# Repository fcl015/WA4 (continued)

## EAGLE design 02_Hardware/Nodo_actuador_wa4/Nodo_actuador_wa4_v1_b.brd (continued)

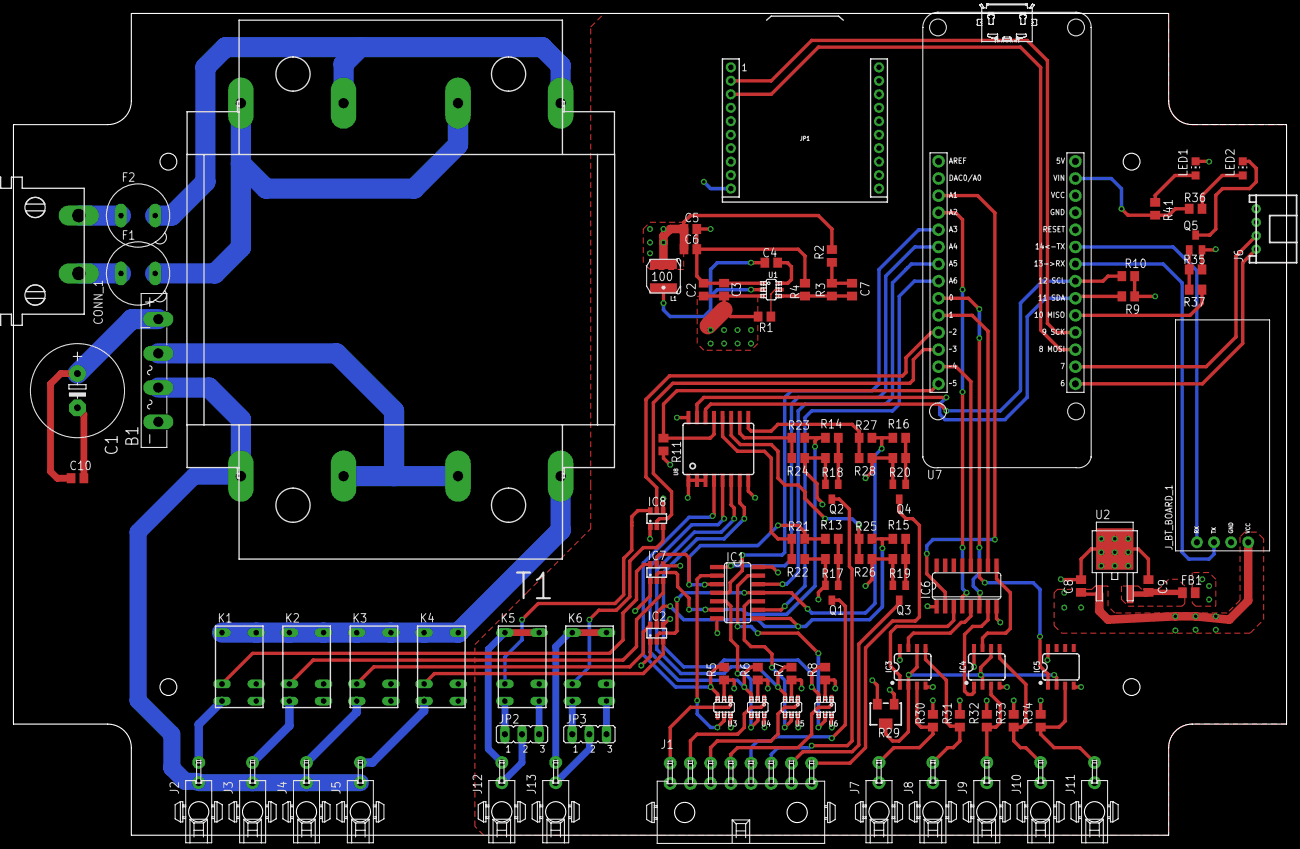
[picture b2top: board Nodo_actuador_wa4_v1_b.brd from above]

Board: 4 copper layers, 189.0 x 122.0 mm, 100 parts (0 on the bottom side), 99 nets.

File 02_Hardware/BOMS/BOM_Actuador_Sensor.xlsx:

BOM: NODO ACTUADOR WA4 V1
Cantidad | Componente | Descripcion | Valor | No. Parte | Fabricante | Link | Costo unitario | Costo total | Aplicación | Notas
1 | CONN_1 | Conector AC C-8 | - | 2570-2210 | Schurter | Mouser | 0.88400000000000001 | 0.88400000000000001 | Conector de alimentacion principal
1 | T1 | Transformador | 24 V 48VA | FP24-2000 | Triad Magnetics | Mouser | 22.97 | 22.97 | Fuente de alimentacion principal
1 | B1 | Puente rectificador | 4A | GBU4J | ON Semiconductor | Mouser | 1.52 | 1.52 | Fuente de alimentacion principal
1 | U1 | Regulador Buck | 500 KHz | TPS54202HDDCR | Texas Instruments | Mouser | 2.1800000000000002 | 2.1800000000000002 | Fuente de 5V
1 | C1 | Capacitor electrolitico | 1000 uF 25V | ECA-1EHG102 | Panasonic | Mouser | 0.96199999999999997 | 0.96199999999999997
2 | C2,C10 | Capacitor ceramico | 10 uF 16V | GRM21BC81C106KA73L | Murata | Mouser | 0.66300000000000003 | 1.3260000000000001
3 | C3,C4,C9 | Capacitor ceramico | 0.1 uF | 08053C104KAT2A | AVX | Mouser | 0.23400000000000001 | 0.70200000000000007
1 | R1 | Resistencia | 510 kΩ | RR1220P-514-D | Susumu | Mouser | 0.13 | 0.13
1 | R2 | Resistencia | 51 Ω | RR1220Q-510-D | Susumu | Mouser | 0.13 | 0.13
1 | R3 | Resistencia | 100 kΩ | RR1220P-104-D | Susumu | Mouser | 0.13 | 0.13
1 | R4 | Resistencia | 13.3 kΩ | RR1220P-1332-D-M | Susumu | Mouser | 0.14299999999999999 | 0.14299999999999999
2 | C5,C6 | Capacitor ceramico | 22 uF 6.3V | GRM219R60J226MEA0D | Murata | Mouser | 0.46800000000000003 | 0.93600000000000005
1 | C7 | Capacitor ceramico | 75 pF | 08051A750JAT2A | AVX | Mouser | 0.377 | 0.377
1 | L1 | Inductor | 15 uH | VLS5045EX-150M-CA | TDK | Mouser | 0.754 | 0.754
1 | C8 | Capacitor ceramico | 0.33 uF | 885012207048 | Wurth Electronics | Mouser | 0.14299999999999999 | 0.14299999999999999
1 | U2 | Regulador lineal | 3.3V | UA78M33IKVURG3 | Texas Instruments | Mouser | 1.01 | 1.01 | Fuente de 3.3V
40 | - | Contacto para cable | - | 1-794606-2 | Te Connectivity | Mouser | 0.10100000000000001 | 4.04 | Contactos para cables de botones, LEDs, sensores de flujo y valvulas
1 |  | Conector hembra 16 pin | 16 pin 2 rows | 4-794619-6 | Te Connectivity | Mouser | 3.17 | 3.17 | Conector para botones y LEDs
1 | - | Conector macho 16 pin | 16 pin 2 rows | 1-794617-6 | Te Connectivity | Mouser | 1.1399999999999999 | 1.1399999999999999 | Conector para botones y LEDs
11 |  | Conector hembra 2 pin | 2 pin 2 rows | 3-794618-2 | Te Connectivity | Mouser | 1 | 11 | Conectores para valvulas y sensores
11 | - | Conector macho 2 pin | 2 pin 2 rows | 794617-2 | Te Connectivity | Mouser | 0.66300000000000003 | 7.2930000000000001 | Conectores para valvulas y sensores
1 | IC1 | Puertas lógicas 2-6V Quad OR | - | MC74HC32ADR2G | ON Semiconductor | Mouser | 0.55900000000000005 | 0.55900000000000005 | Para control de valvulas por boton o por software
4 | U3-U6 | Controlador push button | - | MAX16054AZT+T | Maxim Integrated | Mouser | 3.37 | 13.48 | Eliminación de rebote y proteccion ESD
17 | R5-R11,R17-R20,R22,R24,R26,R28,R35,R37 | Resistencia | 10 kΩ | RR1220P-103-D | Susumu | Mouser | 0.13 | 2.21
6 | K1-K6 | Relevador | 5 VDC | G5V-1-2 DC5 | Omron | Mouser | 2.85 | 17.100000000000001 | Relevadores para valvulas y activacion de bomba
3 | IC2,IC7,IC8 | Driver relevador | - | MDC3105DMT1G | ON Semiconductor | Mouser | 0.57199999999999995 | 1.7159999999999997
4 | R13-R16 | Resistencia | 1 kΩ | RR1220P-102-D | Susumu | Mouser | 0.13 | 0.52
5 | Q1-Q5 | Transistor BJT NPN | - | BCX70K | ON Semiconductor | Mouser | 0.377 | 1.885 | Encendido de LEDs de los botones
4 | - | Push button con LED | Azul | 481 | Adafruit | Mouser / Adafruit | 6.44 | 25.76 | Botones para encendido manual de valvulas
2 | JP1 | XBEE Header | 10 pin | 366 | Adafruit | Mouser | 1.24 | 2.48 | Socket Xbee
1 | R29 | Potenciometro | 50 kΩ | PVG5A503C03B00 | Bourns | Mouser | 3.3 | 3.3 | Referencia de voltaje para sensores de flujo
4 | R21,R23,R25,R27 | Resistencia | 5.1 kΩ | RR1220P-512-D | Susumu | Mouser | 0.13 | 0.52
3 | IC3,IC4,IC5 | Amplificador operacional | - | LM358ADR | Texas Instruments | Mouser | 0.46800000000000003 | 1.4040000000000001 | Lectura de sensor de flujo
1 | IC6 | Buffer no inversor | - | CD4050BDR | Texas Instruments | Mouser | 0.54600000000000004 | 0.54600000000000004 | Acondicionamiento de señal de sensor de flujo
5 | R30-R34 | Resistencia | 330 Ω 0.5W 0.5% | SG73G2ATTD3300D | KOA | Mouser | 0.29899999999999999 | 1.4949999999999999
2 | LED1-LED2 | LED | Verde | LTST-C170GKT | Lite On | Mouser | 0.39 | 0.78 | Indicadores
2 | R36,R41 | Resistencia | 330 Ω | RR1220P-331-D | Susumu | Mouser | 0.13 | 0.26
1 | U8 | Expansion IO | - | PCF8574DWR | Texas Instruments | Mouser | 1.95 | 1.95
2 | - | Header Arduino | 14 pin | M20-7821446 | Harwin | Mouser | 1.87 | 3.74
1 | FB1 | Ferrita | - | MPZ2012S102JTD25 | TDK | Mouser | 0.16900000000000001 | 0.16900000000000001
1 | - | Header | 4 pin | M20-7820446 | Harwin | Mouser | 1.03 | 1.03
1 | - | Antenna con cable | - | ANT-916-PML-UFL | Linx Technologies | Mouser | 12.74 | 12.74
 |  |  |  |  |  |  | Total | 154.584

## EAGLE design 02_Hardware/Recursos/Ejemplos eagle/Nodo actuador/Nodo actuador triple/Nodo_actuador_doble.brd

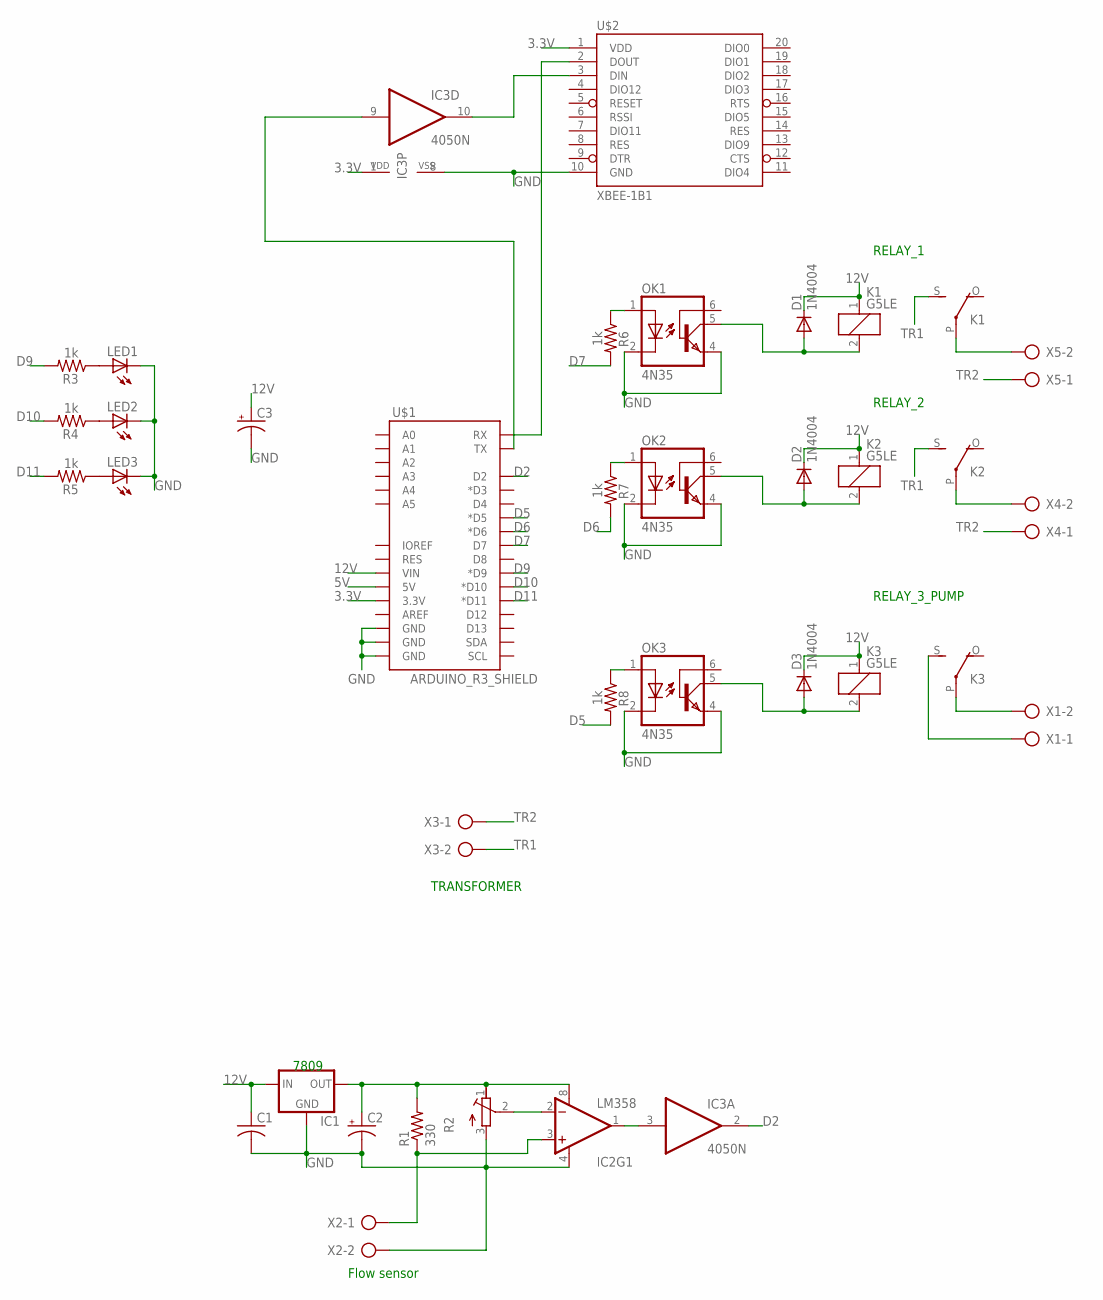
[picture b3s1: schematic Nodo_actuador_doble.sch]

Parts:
C1: C-US050-024X044; C050-024X044
C2, C3: CPOL-USE2.5-6; E2,5-6
D1, D2, D3: 1N4004; DO41-10
IC1: 78XXS
IC2: LM358; DIP08
IC3: 4050N; DIL16
K1, K2, K3: G5LE
LED1, LED2, LED3: LED3MM
OK1, OK2, OK3: 4N35; DIL06
R1: 330; 0204/7
R2: R-TRIMMT93YA; RTRIMT93YA
R3, R4, R5, R6, R7, R8: 1k; 0204/7
U$1: ARDUINO_R3_SHIELD; UNO_R3_SHIELD
U$2: XBEE-1B1; XBEE-1
X1, X2, X3, X4, X5: AK500/2

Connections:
3.3V: IC3.1 (VDD), U$1.3.3V, U$2.1 (VDD)
5V: U$1.5V
12V: C1.1, C3.+, D1.C, D2.C, D3.C, IC1.IN, K1.1, K2.1, K3.1, U$1.VIN
D2: IC3.2 (O), U$1.D2
D5: R8.2, U$1.D5 (*D5)
D6: R7.2, U$1.D6 (*D6)
D7: R6.2, U$1.D7
D9: R3.2, U$1.D9 (*D9)
D10: R4.2, U$1.D10 (*D10)
D11: R5.2, U$1.D11 (*D11)
GND: C1.2, C2.-, C3.-, IC1.GND, IC2.4 (V-), IC3.8 (VSS), LED1.K (C), LED2.K (C), LED3.K (C), OK1.2 (C), OK1.4 (EMI), OK2.2 (C), OK2.4 (EMI), OK3.2 (C), OK3.4 (EMI), R2.3 (E), U$1.GND@0 (GND), U$1.GND@1 (GND), U$1.GND@2 (GND), U$2.10 (GND), X2.2
unnamed: LED1.A, R3.1
unnamed: LED2.A, R4.1
unnamed: LED3.A, R5.1
unnamed: IC2.3 (+IN), R1.1, X2.1
unnamed: C2.+, IC1.OUT, IC2.8 (V+), R1.2, R2.1 (A)
unnamed: IC2.1 (OUT), IC3.3 (I)
unnamed: IC2.2 (-IN), R2.2 (S)
unnamed: K1.P, X5.2
unnamed: D1.A, K1.2, OK1.5 (COL)
unnamed: K2.P, X4.2
unnamed: D2.A, K2.2, OK2.5 (COL)
unnamed: U$1.RX, U$2.2 (DOUT)
unnamed: IC3.9 (I), U$1.TX
unnamed: IC3.10 (O), U$2.3 (DIN)
unnamed: D3.A, K3.2, OK3.5 (COL)
unnamed: K3.P, X1.2
unnamed: K3.S, X1.1
unnamed: OK1.1 (A), R6.1
unnamed: OK2.1 (A), R7.1
unnamed: OK3.1 (A), R8.1
TR1: K1.S, K2.S, X3.2
TR2: X3.1, X4.1, X5.1

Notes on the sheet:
7809
Flow sensor
TRANSFORMER
RELAY_1
RELAY_2
RELAY_3_PUMP

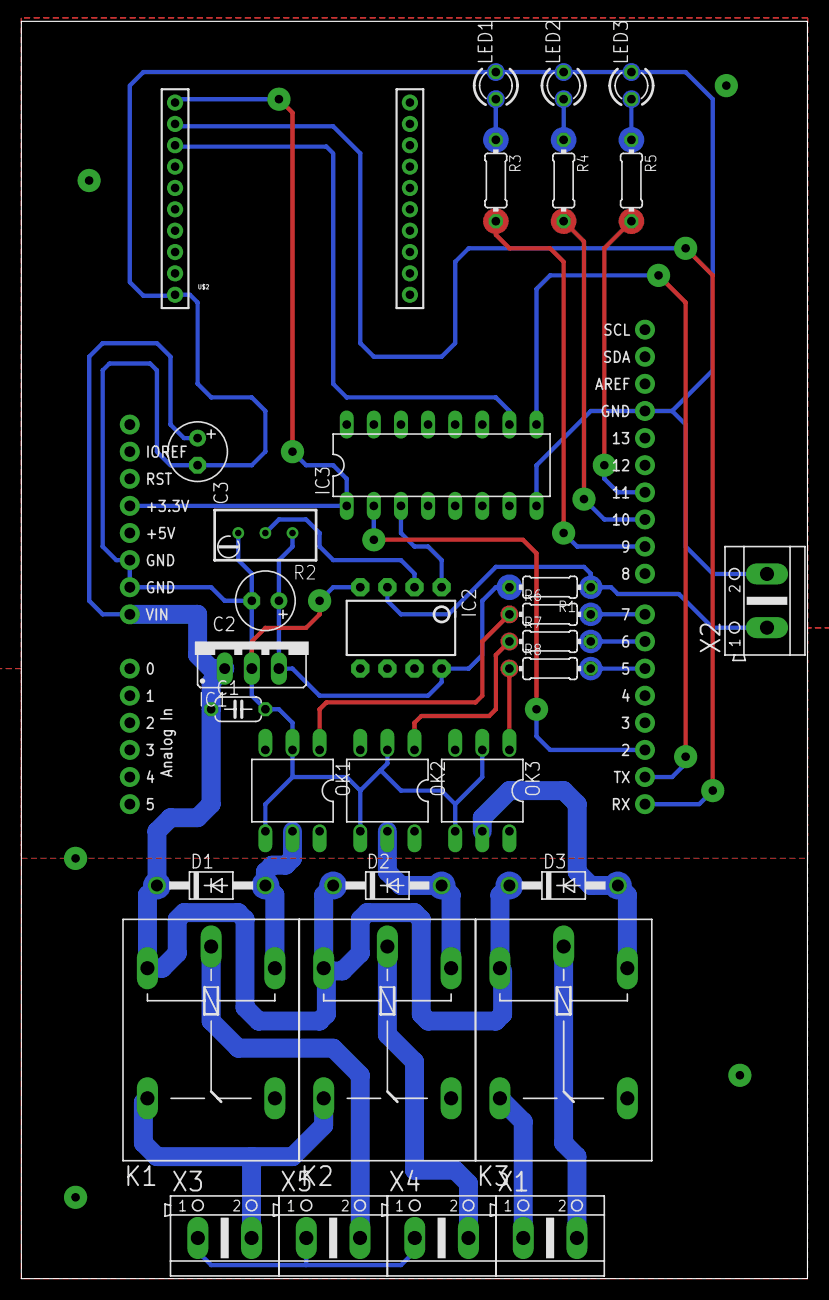
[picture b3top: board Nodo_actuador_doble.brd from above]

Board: 2 copper layers, 73.6 x 117.8 mm, 33 parts (0 on the bottom side), 32 nets.

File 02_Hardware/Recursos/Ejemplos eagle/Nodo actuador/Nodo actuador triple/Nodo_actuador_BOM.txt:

Partlist exported from C:/Users/Carlos/Documents/eagle/Nodo actuador triple/Nodo_actuador_doble.sch at 12/04/2015 02:19:37 p. m.

Part Value             Device            Package       Description                                     MF                      MPN  OC_FARNELL OC_NEWARK PROD_ID 
C1                     C-US050-024X044   C050-024X044  CAPACITOR, American symbol                                                                                
C2                     CPOL-USE2.5-6     E2,5-6        POLARIZED CAPACITOR, American symbol                                                                      
C3                     CPOL-USE2.5-6     E2,5-6        POLARIZED CAPACITOR, American symbol                                                                      
D1   1N4004            1N4004            DO41-10       DIODE                                                                                                     
D2   1N4004            1N4004            DO41-10       DIODE                                                                                                     
D3   1N4004            1N4004            DO41-10       DIODE                                                                                                     
IC1                    78XXS             78XXS         VOLTAGE REGULATOR                                                                                         
IC2  LM358             LM358             DIP08         Jellybean op-amp                                                                                  IC-09172
IC3  4050N             4050N             DIL16         Hex non-inverting BUFFER                                                                                  
K1   G5LE              G5LE              G5LE          RELAY                                                                        unknown    unknown           
K2   G5LE              G5LE              G5LE          RELAY                                                                        unknown    unknown           
K3   G5LE              G5LE              G5LE          RELAY                                                                        unknown    unknown           
LED1                   LED3MM            LED3MM        LED                                                                                                       
LED2                   LED3MM            LED3MM        LED                                                                                                       
LED3                   LED3MM            LED3MM        LED                                                                                                       
OK1  4N35              4N35              DIL06         MOTOROLA OPTO COUPLER                           FAIRCHILD SEMICONDUCTOR 4N35 1328375    72K9946           
OK2  4N35              4N35              DIL06         MOTOROLA OPTO COUPLER                           FAIRCHILD SEMICONDUCTOR 4N35 1328375    72K9946           
OK3  4N35              4N35              DIL06         MOTOROLA OPTO COUPLER                           FAIRCHILD SEMICONDUCTOR 4N35 1328375    72K9946           
R1   330               R-US_0204/7       0204/7        RESISTOR, American symbol                                                                                 
R2                     R-TRIMMT93YA      RTRIMT93YA    Trimm resistor                                                                                            
R3   1k                R-US_0204/7       0204/7        RESISTOR, American symbol                                                                                 
R4   1k                R-US_0204/7       0204/7        RESISTOR, American symbol                                                                                 
R5   1k                R-US_0204/7       0204/7        RESISTOR, American symbol                                                                                 
R6   1k                R-US_0204/7       0204/7        RESISTOR, American symbol                                                                                 
R7   1k                R-US_0204/7       0204/7        RESISTOR, American symbol                                                                                 
R8   1k                R-US_0204/7       0204/7        RESISTOR, American symbol                                                                                 
U$1  ARDUINO_R3_SHIELD ARDUINO_R3_SHIELD UNO_R3_SHIELD Shield form compatible with the Arduino Uno R3.                                                           
U$2  XBEE-1B1          XBEE-1B1          XBEE-1        Xbee module footprints                                                                                    
X1                     AK500/2           AK500/2       CONNECTOR                                                                    unknown    unknown           
X2                     AK500/2           AK500/2       CONNECTOR                                                                    unknown    unknown           
X3                     AK500/2           AK500/2       CONNECTOR                                                                    unknown    unknown           
X4                     AK500/2           AK500/2       CONNECTOR                                                                    unknown    unknown           
X5                     AK500/2           AK500/2       CONNECTOR                                                                    unknown    unknown

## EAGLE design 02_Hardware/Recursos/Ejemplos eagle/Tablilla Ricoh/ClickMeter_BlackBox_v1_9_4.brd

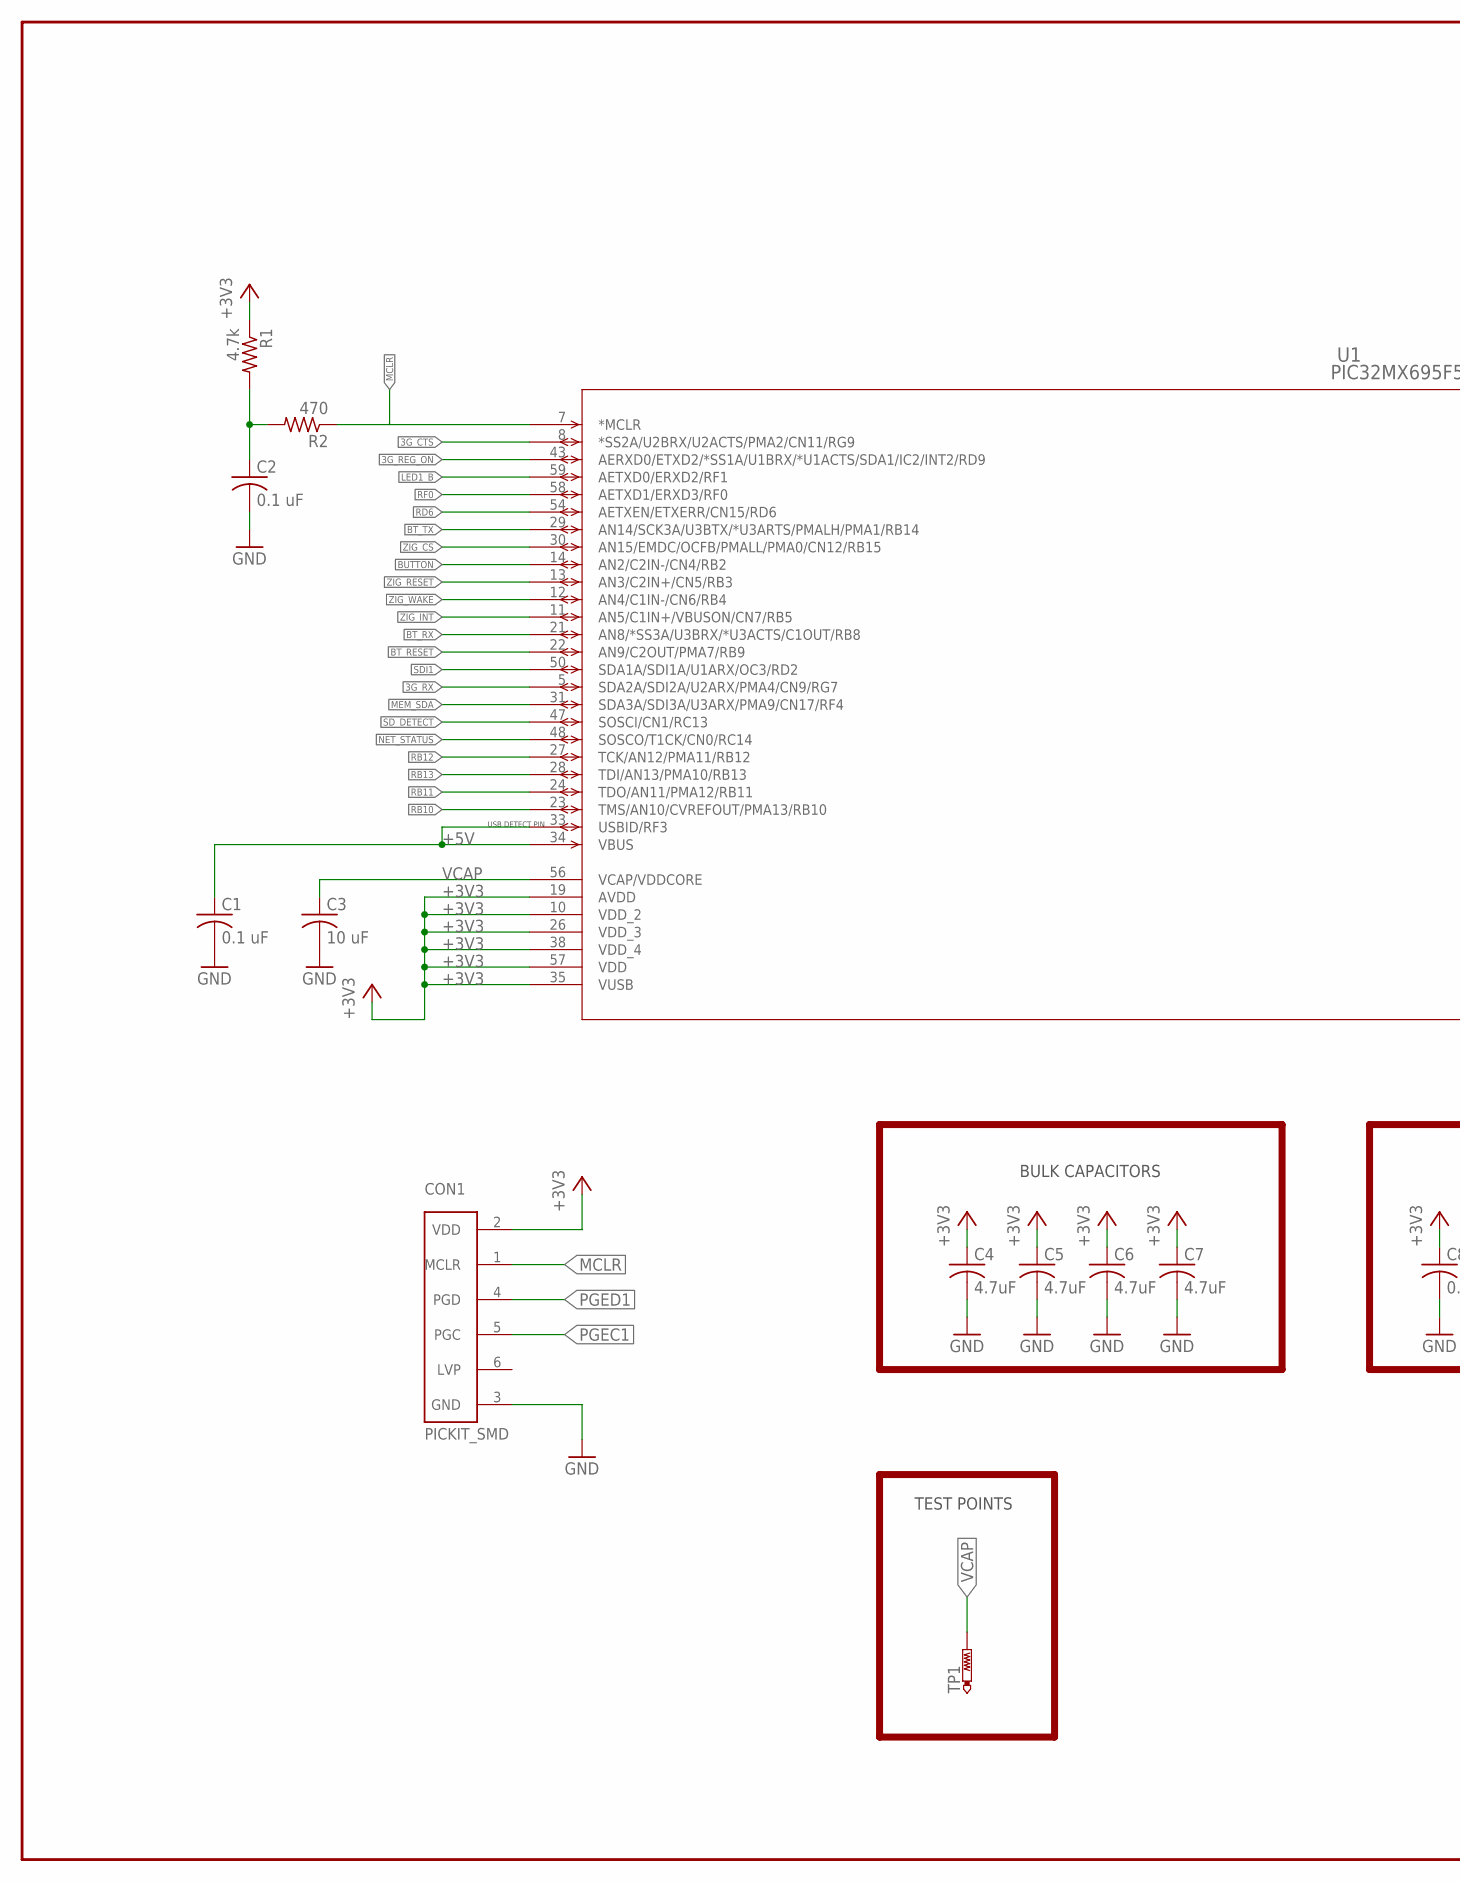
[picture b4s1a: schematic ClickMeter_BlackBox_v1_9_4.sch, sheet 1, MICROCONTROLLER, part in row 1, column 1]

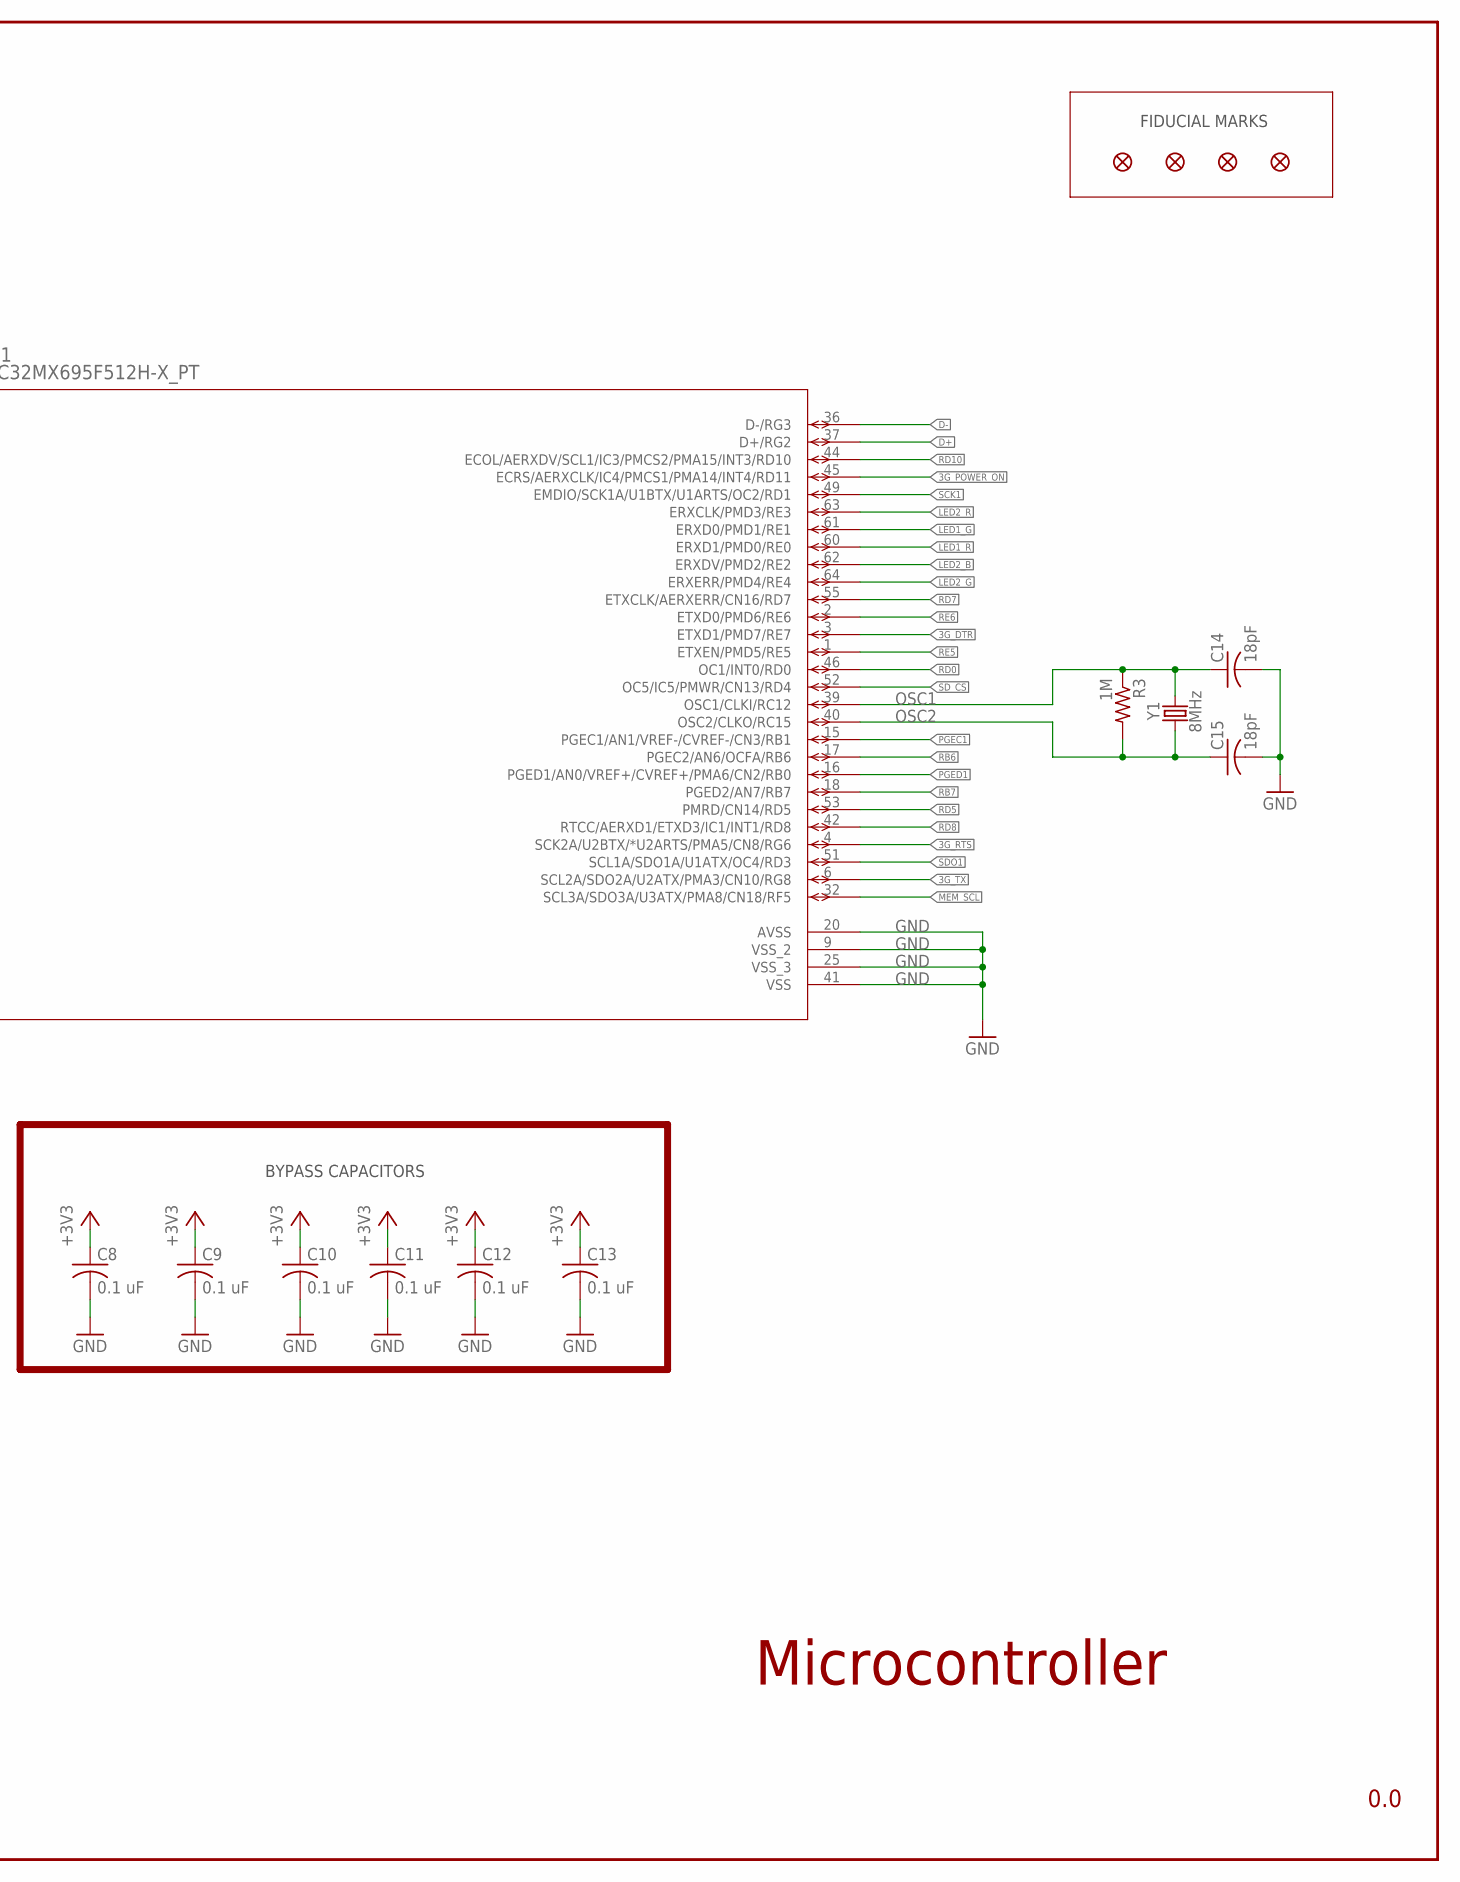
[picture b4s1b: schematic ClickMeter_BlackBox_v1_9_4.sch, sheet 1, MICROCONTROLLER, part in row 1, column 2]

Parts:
C1, C2, C8, C9, C10, C11, C12, C13: 0.1 uF; C0603
C3: 10 uF; C0805
C4, C5, C6, C7: 4.7uF; C0603
C14, C15: 18pF; C0603
CON1: PICKIT_SMD; SMD_PICKIT
F1, F2, F3, F4: FIDUCIAL
R1: 4.7k; R0603
R2: 470; R0603
R3: 1M; R0603
TP1: PTR1B1,27; B1,27
U1: PIC32MX695F512H-X_PT; TQFP64_10X10MC
Y1: 8MHz; CRYSTAL-TXC-7A

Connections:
3G_CTS: U1.8 (*SS2A/U2BRX/U2ACTS/PMA2/CN11/RG9); also elsewhere on the board
3G_DTR: U1.3 (ETXD1/PMD7/RE7); also elsewhere on the board
3G_POWER_ON: U1.45 (ECRS/AERXCLK/IC4/PMCS1/PMA14/INT4/RD11); also elsewhere on the board
3G_REG_ON: U1.43 (AERXD0/ETXD2/*SS1A/U1BRX/*U1ACTS/SDA1/I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)
3G_RTS: U1.4 (SCK2A/U2BTX/*U2ARTS/PMA5/CN8/RG6); also elsewhere on the board
3G_RX: U1.5 (SDA2A/SDI2A/U2ARX/PMA4/CN9/RG7); also elsewhere on the board
3G_TX: U1.6 (SCL2A/SDO2A/U2ATX/PMA3/CN10/RG8); also elsewhere on the board
+3V3: C4.1, C5.1, C6.1, C7.1, C8.1, C9.1, C10.1, C11.1, C12.1, C13.1, CON1.2 (VDD), R1.1, U1.10 (VDD_2), U1.19 (AVDD), U1.26 (VDD_3), U1.35 (VUSB), U1.38 (VDD_4), U1.57 (VDD); also elsewhere on the board
+5V: C1.1, U1.33 (USBID/RF3), U1.34 (VBUS); also elsewhere on the board
BT_RESET: U1.22 (AN9/C2OUT/PMA7/RB9); also elsewhere on the board
BT_RX: U1.21 (AN8/*SS3A/U3BRX/*U3ACTS/C1OUT/RB8); also elsewhere on the board
BT_TX: U1.29 (AN14/SCK3A/U3BTX/*U3ARTS/PMALH/PMA1/RB14); also elsewhere on the board
BUTTON: U1.14 (AN2/C2IN-/CN4/RB2); also elsewhere on the board
D+: U1.37 (D+/RG2); also elsewhere on the board
D-: U1.36 (D-/RG3); also elsewhere on the board
GND: C1.2, C2.2, C3.2, C4.2, C5.2, C6.2, C7.2, C8.2, C9.2, C10.2, C11.2, C12.2, C13.2, C14.2, C15.2, CON1.3 (GND), U1.9 (VSS_2), U1.20 (AVSS), U1.25 (VSS_3), U1.41 (VSS); also elsewhere on the board
LED1_B: U1.59 (AETXD0/ERXD2/RF1); also elsewhere on the board
LED1_G: U1.61 (ERXD0/PMD1/RE1); also elsewhere on the board
LED1_R: U1.60 (ERXD1/PMD0/RE0); also elsewhere on the board
LED2_B: U1.62 (ERXDV/PMD2/RE2); also elsewhere on the board
LED2_G: U1.64 (ERXERR/PMD4/RE4); also elsewhere on the board
LED2_R: U1.63 (ERXCLK/PMD3/RE3); also elsewhere on the board
MCLR: CON1.1 (MCLR), R2.1, U1.7 (*MCLR)
MEM_SCL: U1.32 (SCL3A/SDO3A/U3ATX/PMA8/CN18/RF5); also elsewhere on the board
MEM_SDA: U1.31 (SDA3A/SDI3A/U3ARX/PMA9/CN17/RF4); also elsewhere on the board
unnamed: C2.1, R1.2, R2.2
NET_STATUS: U1.48 (SOSCO/T1CK/CN0/RC14); also elsewhere on the board
OSC1: C14.1, R3.1, U1.39 (OSC1/CLKI/RC12), Y1.P$2 (2)
OSC2: C15.1, R3.2, U1.40 (OSC2/CLKO/RC15), Y1.P$1 (1)
PGEC1: CON1.5 (PGC), U1.15 (PGEC1/AN1/VREF-/CVREF-/CN3/RB1)
PGED1: CON1.4 (PGD), U1.16 (PGED1/AN0/VREF+/CVREF+/PMA6/CN2/RB0)
RB6: U1.17 (PGEC2/AN6/OCFA/RB6)
RB7: U1.18 (PGED2/AN7/RB7)
RB10: U1.23 (TMS/AN10/CVREFOUT/PMA13/RB10)
RB11: U1.24 (TDO/AN11/PMA12/RB11)
RB12: U1.27 (TCK/AN12/PMA11/RB12)
RB13: U1.28 (TDI/AN13/PMA10/RB13)
RD0: U1.46 (OC1/INT0/RD0)
RD5: U1.53 (PMRD/CN14/RD5)
RD6: U1.54 (AETXEN/ETXERR/CN15/RD6)
RD7: U1.55 (ETXCLK/AERXERR/CN16/RD7)
RD8: U1.42 (RTCC/AERXD1/ETXD3/IC1/INT1/RD8)
RD10: U1.44 (ECOL/AERXDV/SCL1/IC3/PMCS2/PMA15/INT3/R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)
RE5: U1.1 (ETXEN/PMD5/RE5)
RE6: U1.2 (ETXD0/PMD6/RE6)
RF0: U1.58 (AETXD1/ERXD3/RF0)
SCK1: U1.49 (EMDIO/SCK1A/U1BTX/U1ARTS/OC2/RD1); also elsewhere on the board
SDI1: U1.50 (SDA1A/SDI1A/U1ARX/OC3/RD2); also elsewhere on the board
SDO1: U1.51 (SCL1A/SDO1A/U1ATX/OC4/RD3); also elsewhere on the board
SD_CS: U1.52 (OC5/IC5/PMWR/CN13/RD4); also elsewhere on the board
SD_DETECT: U1.47 (SOSCI/CN1/RC13); also elsewhere on the board
VCAP: C3.1, TP1.TP, U1.56 (VCAP/VDDCORE)
ZIG_CS: U1.30 (AN15/EMDC/OCFB/PMALL/PMA0/CN12/RB15)
ZIG_INT: U1.11 (AN5/C1IN+/VBUSON/CN7/RB5)
ZIG_RESET: U1.13 (AN3/C2IN+/CN5/RB3)
ZIG_WAKE: U1.12 (AN4/C1IN-/CN6/RB4)

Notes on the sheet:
BULK CAPACITORS
BYPASS CAPACITORS
Microcontroller
0.0
USB DETECT PIN
FIDUCIAL MARKS
TEST POINTS

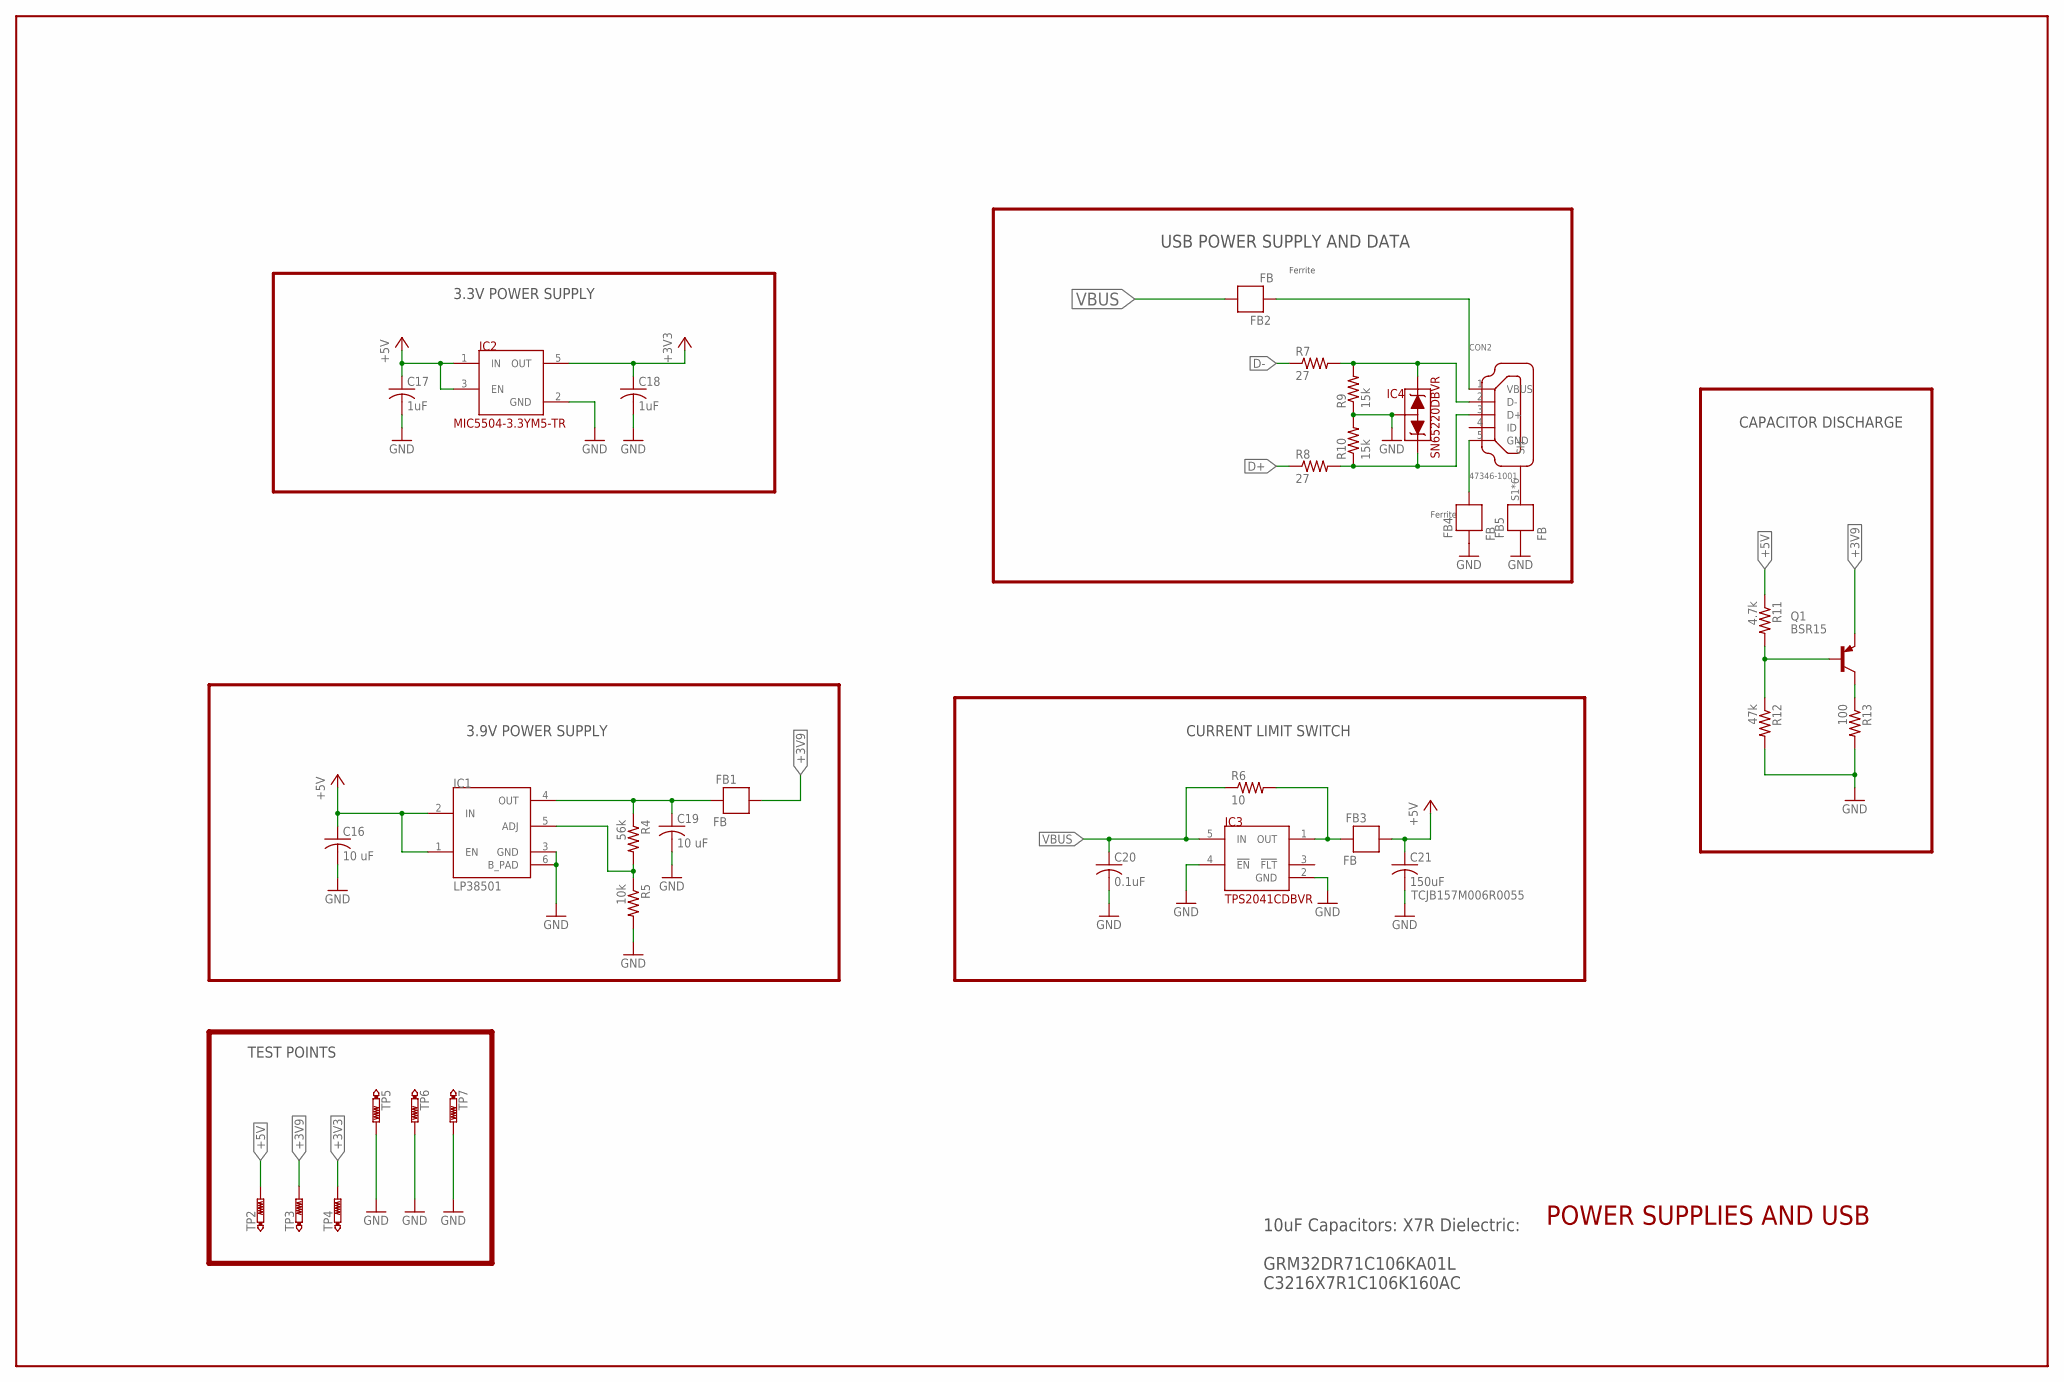
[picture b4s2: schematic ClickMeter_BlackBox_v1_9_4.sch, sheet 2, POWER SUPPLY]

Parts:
C16, C19: 10 uF; C0805
C17, C18: 1uF; C0603
C20: 0.1uF; C0603
C21: 150uF; C1210
CON2: 47346-1001
FB1, FB2, FB3, FB4, FB5: FB; 0603
IC1: LP38501; TO-263-5
IC2: MIC5504-3.3YM5-TR; SOT-23-5
IC3: TPS2041CDBVR; SOT-23-5
IC4: SN65220DBVR; SOT-23-6
Q1: BSR15; SOT23
R4: 56k; R0603
R5: 10k; R0603
R6: 10; R2010
R7, R8: 27; R0603
R9, R10: 15k; R0603
R11: 4.7k; R0603
R12: 47k; R0603
R13: 100; R0603
TP2, TP3, TP4, TP5, TP6, TP7: PTR1B1,27; B1,27

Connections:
+3V3: C18.1, IC2.5 (OUT), TP4.TP; also elsewhere on the board
+3V9: FB1.1, Q1.2 (E), TP3.TP; also elsewhere on the board
+5V: C16.1, C17.1, C21.1, FB3.1, IC1.1 (EN), IC1.2 (IN), IC2.1 (IN), IC2.3 (EN), R11.1, TP2.TP; also elsewhere on the board
D+: R8.1; also elsewhere on the board
D-: R7.1; also elsewhere on the board
GND: C16.2, C17.2, C18.2, C19.2, C20.2, C21.2, FB4.2, FB5.2, IC1.3 (GND), IC1.6 (B_PAD), IC2.2 (GND), IC3.2 (GND), IC3.4 (!EN!), IC4.2 (GND), IC4.5 (GND), R5.2, R9.1, R10.2, R12.2, R13.2, TP5.TP, TP6.TP, TP7.TP; also elsewhere on the board
unnamed: C19.1, FB1.2, IC1.4 (OUT), R4.1
unnamed: IC1.5 (ADJ), R4.2, R5.1
unnamed: CON2.1 (VBUS), FB2.2
unnamed: FB3.2, IC3.1 (OUT), R6.2
unnamed: Q1.1 (B), R11.2, R12.1
unnamed: Q1.3 (C), R13.1
unnamed: CON2.S1 (SH), CON2.S2 (SH), CON2.S3 (SH), CON2.S4 (SH), CON2.S5 (SH), CON2.S6 (SH), FB5.1
unnamed: CON2.5 (GND), FB4.1
unnamed: CON2.2 (D-), IC4.4 (B), R7.2, R9.2
unnamed: CON2.3 (D+), IC4.6 (A), R8.2, R10.1
VBUS: C20.1, FB2.1, IC3.5 (IN), R6.1

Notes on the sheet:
3.3V POWER SUPPLY
10uF Capacitors: X7R Dielectric: GRM32DR71C106KA01L C3216X7R1C106K160AC
3.9V POWER SUPPLY
Ferrite
CURRENT LIMIT SWITCH
USB POWER SUPPLY AND DATA
POWER SUPPLIES AND USB
CAPACITOR DISCHARGE
TEST POINTS
TCJB157M006R0055
